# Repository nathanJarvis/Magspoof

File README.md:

Desgined by Nathan Jarvis, Jonathon Severns

Improvements on Magspoof Design

-includes switching cards with indicator LED

-card expansion

-PCB Design

-battery kill switch

-case for the device

Project based on  Samy Kamkar

Project Site: https://samy.pl/magspoof/

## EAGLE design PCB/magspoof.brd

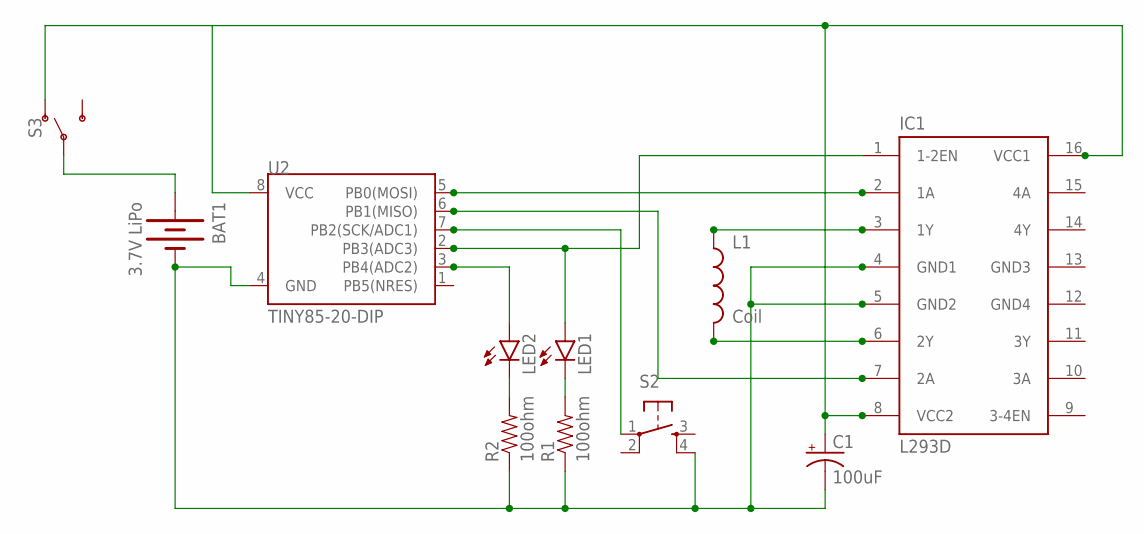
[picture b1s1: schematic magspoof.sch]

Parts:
BAT1: 3.7V LiPo; LIPO-110-TABS
C1: 100uF; CPOL-RADIAL-100UF-25V
IC1: L293D; DIL16
L1: Coil; AXIAL-0.6
LED1, LED2: LED-3MM-NO_SILK; LED3MM-NS
R1, R2: 100ohm; AXIAL-0.3
S2: TAC_SWITCHPTH; TACTILE-PTH
S3: SWITCH-SPDT-PTH-11.6X4.0MM; SWITCH_SPDT_PTH_11.6X4.0MM
U2: TINY85-20-DIP; DIP08_MCU

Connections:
GND: BAT1.-, C1.2 (-), IC1.4 (GND1), IC1.5 (GND2), R1.P$1 (1), R2.P$1 (1), S2.4, U2.4 (GND)
GND3: IC1.13 (GND3)
GND4: IC1.12 (GND4)
unnamed: IC1.3 (1Y), L1.P$1 (1)
unnamed: IC1.6 (2Y), L1.P$2 (2)
unnamed: IC1.2 (1A), U2.5 (PB0(MOSI))
unnamed: IC1.7 (2A), U2.6 (PB1(MISO))
unnamed: IC1.1 (1-2EN), LED1.A, U2.2 (PB3(ADC3))
unnamed: LED2.K (C), R2.P$2 (2)
unnamed: LED1.K (C), R1.P$2 (2)
unnamed: S2.1, S2.2, U2.7 (PB2(SCK/ADC1))
unnamed: LED2.A, U2.3 (PB4(ADC2))
unnamed: BAT1.+, S3.2
unnamed: C1.1 (+), IC1.8 (VCC2), IC1.16 (VCC1), S3.1 (O), U2.8 (VCC)

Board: 2 copper layers, 11 parts (0 on the bottom side), 12 nets, no tracks yet.

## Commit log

2017-12-06 intial commit
2017-12-06 add material
2017-12-06 README.md edited online with Bitbucket
2017-12-06 remove redudant folder
2017-12-06 LibraryURL.txt edited online with Bitbucket
2017-12-06 add case
2017-12-07 add earleir iterations of input

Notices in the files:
parts and their libraries:
SparkFun-Electromechanical: Licensing: Creative Commons ShareAlike 4.0 International - https://creativecommons.org/licenses/by-sa/4.0
